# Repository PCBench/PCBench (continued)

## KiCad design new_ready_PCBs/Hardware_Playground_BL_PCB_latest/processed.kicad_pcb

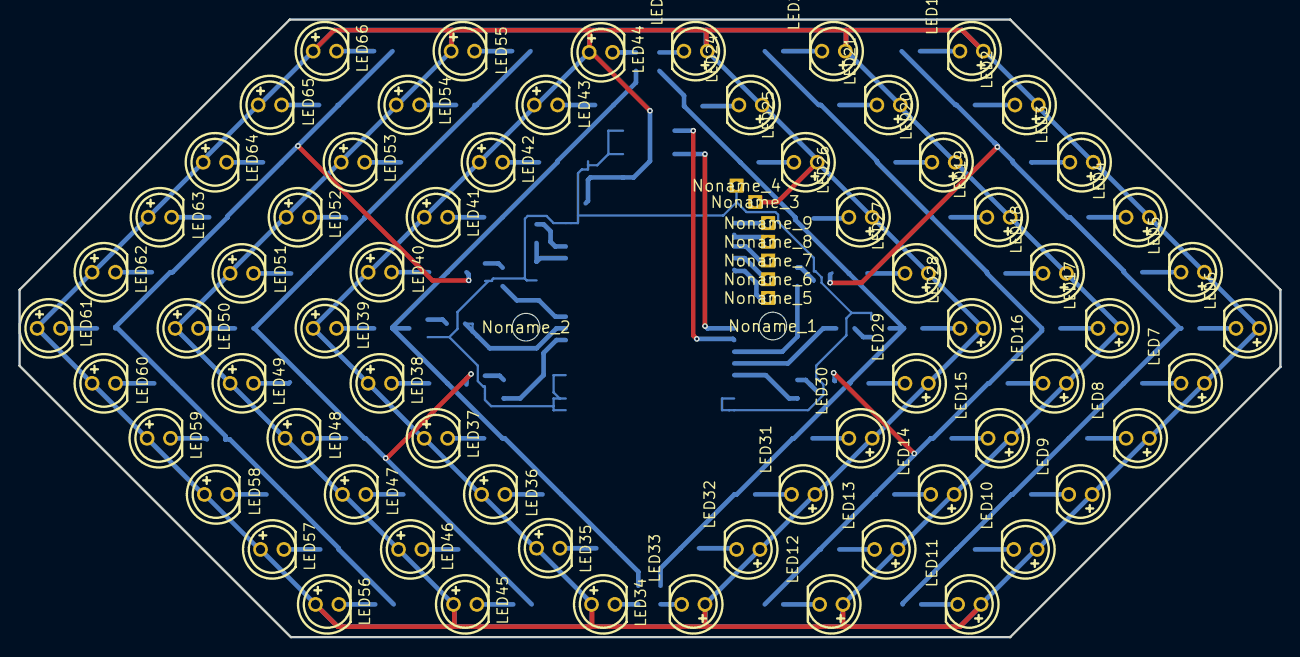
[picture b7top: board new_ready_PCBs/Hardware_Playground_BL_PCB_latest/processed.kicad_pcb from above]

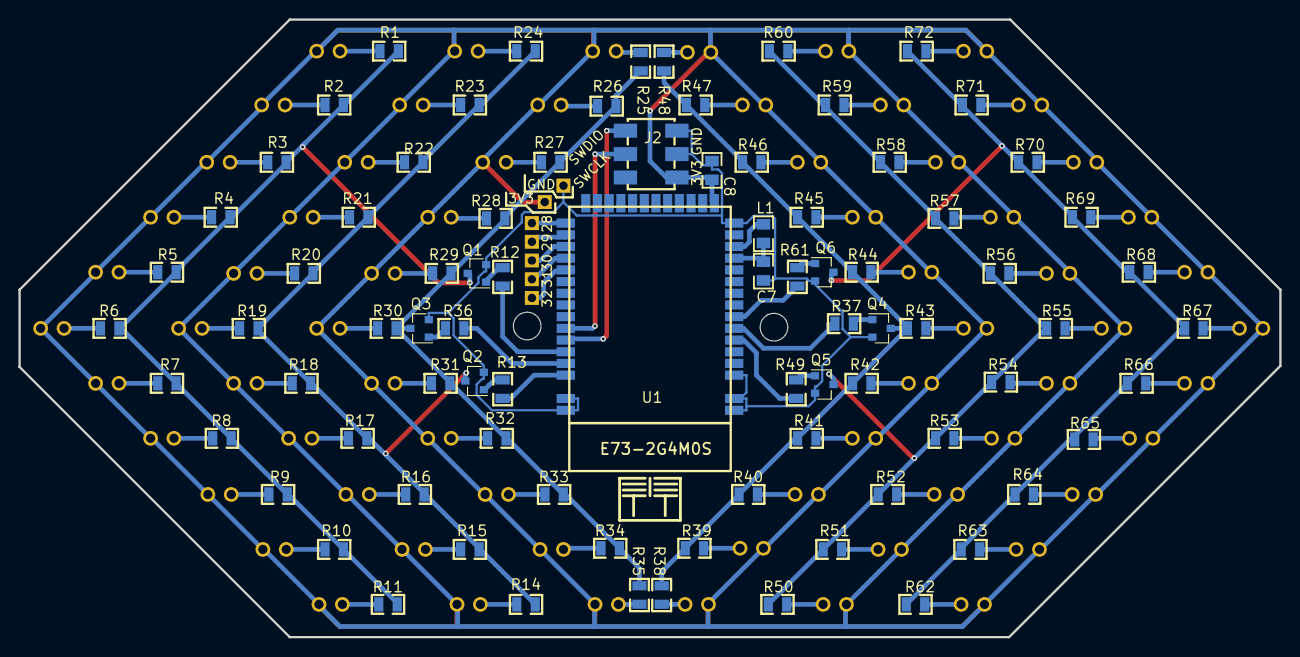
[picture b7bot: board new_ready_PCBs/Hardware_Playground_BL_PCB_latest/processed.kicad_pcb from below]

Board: 2 copper layers, 136.9 x 67.1 mm, 159 parts (6 on the bottom side), 95 nets.

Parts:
C7: 1u; 0805
C8: 10u; 0805
J2: SWD; H2X3-SMD-2.54
L1: 10uH; 0805
LED1, LED2, LED3, LED4, LED5, LED6, LED7, LED8, LED9, LED10, LED11, LED12, LED13, LED14, LED15, LED16, LED17, LED18, LED19, LED20, LED21, LED22, LED23, LED24, LED25, LED26, LED27, LED28, LED29, LED30, LED31, LED32, LED33, LED34, LED35, LED36, LED37, LED38, LED39, LED40, LED41, LED42, LED43, LED44, LED45, LED46, LED47, LED48, LED49, LED50, LED51, LED52, LED53, LED54, LED55, LED56, LED57, LED58, LED59, LED60, LED61, LED62, LED63, LED64, LED65, LED66: HL-503S45FC; LED-TH_BD5.0-P2.54-FD
LG: my_logo; ggeac4e8891367b2b2c
Noname_1, Noname_2: MountingHole_3.00mm
Noname_3, Noname_4, Noname_5, Noname_6, Noname_7, Noname_8, Noname_9: Pad_1.52mm
Q1, Q2, Q3, Q4, Q5, Q6: MMBT2222; SOT-23
R1, R2, R3, R4, R5, R6, R7, R8, R9, R10, R11, R14, R15, R16, R17, R18, R19, R20, R21, R22, R23, R24, R25, R26, R27, R28, R29, R30, R31, R32, R33, R34, R35, R38, R39, R40, R41, R42, R43, R44, R45, R46, R47, R48, R50, R51, R52, R53, R54, R55, R56, R57, R58, R59, R60, R62, R63, R64, R65, R66, R67, R68, R69, R70, R71, R72: 33; R0805
R12, R13, R36, R37, R49, R61: 1K; R0805
U1: E73-2G4M0S; E73-2G4M04S

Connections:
+3V3: C8.2, J2.1, LED1.1, LED2.1, LED3.1, LED4.1, LED5.1, LED6.1, LED7.1, LED8.1, LED9.1, LED10.1, LED11.1, LED12.1, LED13.1, LED14.1, LED15.1, LED16.1, LED17.1, LED18.1, LED19.1, LED20.1, LED21.1, LED22.1, LED23.1, LED24.1, LED25.1, LED26.1, LED27.1, LED28.1, LED29.1, LED30.1, LED31.1, LED32.1, LED33.1, LED34.1, LED35.1, LED36.1, LED37.1, LED38.1, LED39.1, LED40.1, LED41.1, LED42.1, LED43.1, LED44.1, LED45.1, LED46.1, LED47.1, LED48.1, LED49.1, LED50.1, LED51.1, LED52.1, LED53.1, LED54.1, LED55.1, LED56.1, LED57.1, LED58.1, LED59.1, LED60.1, LED61.1, LED62.1, LED63.1, LED64.1, LED65.1, LED66.1, Noname_3.3, U1.16
AL1: R12.1, U1.39
AL2: R13.1, U1.41
AL3: R36.1, U1.40
AR1: R37.1, U1.6
AR2: R49.1, U1.5
AR3: R61.1, U1.7
C7_2: C7.2, L1.1, U1.12
GND: C7.1, C8.1, J2.2, J2.3, Noname_4.2, Q1.2, Q2.2, Q3.2, Q4.2, Q5.2, Q6.2, U1.0, U1.1, U1.2, U1.15, U1.42, U1.43
L1_2: L1.2, U1.13
LED1_2: LED1.2, R1.2
LED2_2: LED2.2, R2.2
LED3_2: LED3.2, R3.2
LED4_2: LED4.2, R4.2
LED5_2: LED5.2, R5.2
LED6_2: LED6.2, R6.2
LED7_2: LED7.2, R7.2
LED8_2: LED8.2, R8.2
LED9_2: LED9.2, R9.2
LED10_2: LED10.2, R10.2
LED11_2: LED11.2, R11.2
LED23_2: LED23.2, R25.2
LED24_2: LED24.2, R26.2
LED25_2: LED25.2, R27.2
LED26_2: LED26.2, R28.2
LED27_2: LED27.2, R29.2
LED28_2: LED28.2, R30.2
LED29_2: LED29.2, R31.2
LED30_2: LED30.2, R32.2
LED31_2: LED31.2, R33.2
LED32_2: LED32.2, R34.2
LED33_2: LED33.2, R35.2
unnamed: Noname_9.1, U1.28
unnamed: Noname_8.1, U1.29
unnamed: Noname_7.1, U1.30
unnamed: Noname_6.1, U1.31
unnamed: Noname_5.1, U1.32
Q1_1: Q1.1, R12.2
Q2_3: Q2.3, R14.1, R15.1, R16.1, R17.1, R18.1, R19.1, R20.1, R21.1, R22.1, R23.1, R24.1
Q3_1: Q3.1, R36.2
Q4_3: Q4.3, R38.1, R39.1, R40.1, R41.1, R42.1, R43.1, R44.1, R45.1, R46.1, R47.1, R48.1
Q5_3: Q5.3, R50.1, R51.1, R52.1, R53.1, R54.1, R55.1, R56.1, R57.1, R58.1, R59.1, R60.1
Q6_3: Q6.3, R62.1, R63.1, R64.1, R65.1, R66.1, R67.1, R68.1, R69.1, R70.1, R71.1, R72.1
R1_1: Q1.3, R1.1, R2.1, R3.1, R4.1, R5.1, R6.1, R7.1, R8.1, R9.1, R10.1, R11.1
R13_2: Q2.1, R13.2
R14_2: LED12.2, R14.2
R15_2: LED13.2, R15.2
R16_2: LED14.2, R16.2
R17_2: LED15.2, R17.2
R18_2: LED16.2, R18.2
R19_2: LED17.2, R19.2
R20_2: LED18.2, R20.2
R21_2: LED19.2, R21.2
R22_2: LED20.2, R22.2
R23_2: LED21.2, R23.2
R24_2: LED22.2, R24.2
R25_1: Q3.3, R25.1, R26.1, R27.1, R28.1, R29.1, R30.1, R31.1, R32.1, R33.1, R34.1, R35.1
R37_2: Q4.1, R37.2
R38_2: LED34.2, R38.2
R39_2: LED35.2, R39.2
R40_2: LED36.2, R40.2
R41_2: LED37.2, R41.2
R42_2: LED38.2, R42.2
R43_2: LED39.2, R43.2
R44_2: LED40.2, R44.2
R45_2: LED41.2, R45.2
R46_2: LED42.2, R46.2
R47_2: LED43.2, R47.2
R48_2: LED44.2, R48.2
R49_2: Q5.1, R49.2
R50_2: LED45.2, R50.2
R51_2: LED46.2, R51.2
R52_2: LED47.2, R52.2
R53_2: LED48.2, R53.2
R54_2: LED49.2, R54.2
R55_2: LED50.2, R55.2
R56_2: LED51.2, R56.2
R57_2: LED52.2, R57.2
R58_2: LED53.2, R58.2
R59_2: LED54.2, R59.2
R60_2: LED55.2, R60.2
R61_2: Q6.1, R61.2
R62_2: LED56.2, R62.2
R63_2: LED57.2, R63.2
R64_2: LED58.2, R64.2
R65_2: LED59.2, R65.2
R66_2: LED60.2, R66.2
R67_2: LED61.2, R67.2
R68_2: LED62.2, R68.2
R69_2: LED63.2, R69.2
R70_2: LED64.2, R70.2
R71_2: LED65.2, R71.2
R72_2: LED66.2, R72.2
SWCLK: J2.5, U1.37
SWDIO: J2.4, U1.38

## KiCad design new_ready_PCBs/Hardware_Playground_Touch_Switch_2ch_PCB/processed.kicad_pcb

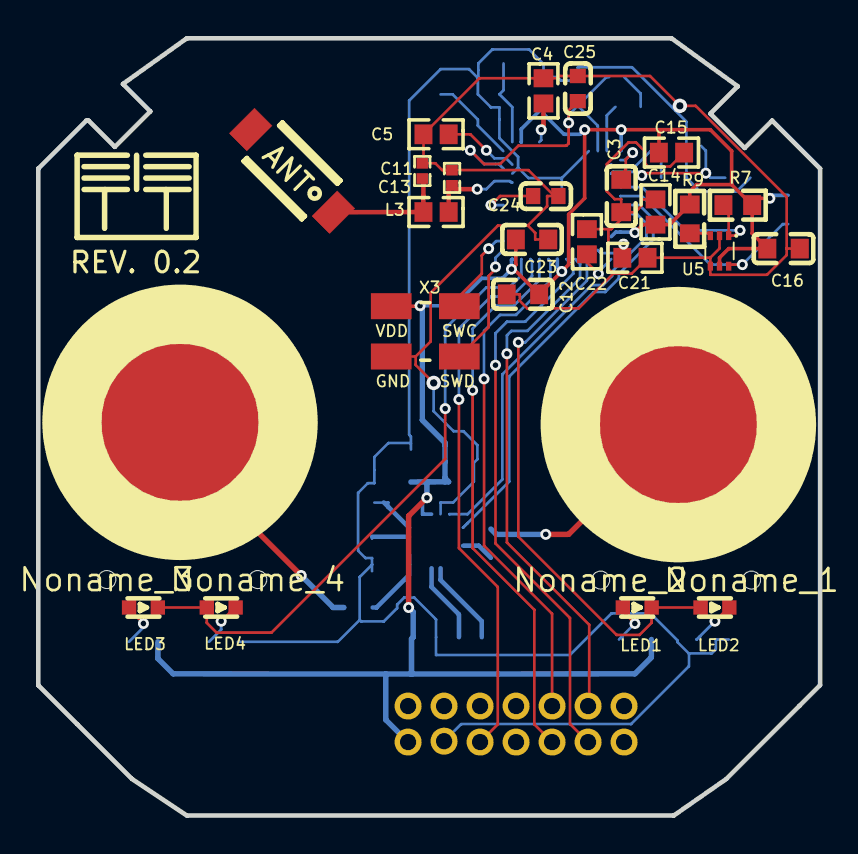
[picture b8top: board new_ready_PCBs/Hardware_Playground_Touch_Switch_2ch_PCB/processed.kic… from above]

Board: 2 copper layers, 43.4 x 43.2 mm, 57 parts (0 on the bottom side), 43 nets.

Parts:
ALG: my_logo; ggeac4e8891367b2b2c
C1, C15, C17: 1uF; 0603
C2, C3, C12, C16, C18, C19, C20, C23: 100nF; C0603
C4: N.C.; 0603
C5: 100pF; 0603
C6: 2.2nF; C0603
C7, C8, C9, C10: 22pF; 0603
C11: 0.8pF; 0402
C13: 0.5pF; 0402
C14, C21, C22: 4.7uF; 0603
C24: 820pF; C0603
C25: 47nF; C0603
CN1: 2X7P; HDR-TH_14P-P2.00-V-R2-C7-S2.00_A2005HWV-2X7P
H1: PROG; CONNECTER_SMD_1.27_1X4_D180
L2: 10uH; 0603
L3: 4.7nH; 0603
L4: 15nH; 0402
LED1, LED3: RED; LED-SMD_0603-T
LED2, LED4: BLUE; LED-SMD_0603-T
Noname_1, Noname_2, Noname_3, Noname_4: MountingHole_1.00mm
R1, R2, R5, R6, R7, R8, R9: 4.7K; R0603
R3, R10: 560; R0603
U1: NRF52840-QIAA-R; AQFN-73_L7.0-W7.0-P0.50-BL-EP4.8
U2, U7: TS1; LIVOLO_TOUCH_PAD
U3: Antenna 2.4GHz; AN6520
U5: TMP112; SOT-563_L1.6-W1.2-P0.50-LS1.6-BL
U6: CY8C4014LQI-421T; QFN-16_L3.0-W3.0-P0.50-BL-EP1.7
X1: 32MHz; OSC-SMD_4P-L2.0-W1.6-BL
X2: 32.768KHz; FC-135R_L3.2-W1.5
X3: ICSP; SWD4_5032

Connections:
ANT: C11.1, L3.1, U1.H23
C4_2: C4.2, U1.A18
CH1_LED: LED1.1, LED2.2, U1.AD8
CH2_LED: LED3.1, LED4.2, U1.AD22
DCC: L2.1, U1.B3
DEC4_6: C1.1, C25.2, L4.2, U1.B5, U1.E24
GND: C1.2, C2.1, C3.2, C4.1, C5.2, C6.2, C7.2, C8.2, C9.1, C10.1, C11.2, C12.1, C13.2, C14.2, C15.1, C16.2, C17.1, C18.1, C19.1, C20.1, C21.1, C22.1, C23.1, C24.1, C25.1, CN1.11, H1.3, R2.2, R5.2, U1.0, U1.B7, U1.F23, U5.2, U5.4, U6.7, X1.2, X1.4, X3.3
L2_2: L2.2, L4.1
L3_2: C13.1, L3.2, U3.1
LED2_1: LED2.1, R5.1
LED3_2: LED3.2, R1.1
MTO1: U1.R1, U6.8
MTO2: U1.N1, U6.9
R1_RST: CN1.6, U1.AD16
R1_SET: CN1.4, U1.AD10
R2_1: LED4.1, R2.1
R2_RST: CN1.3, U1.AD12
R2_SET: CN1.5, U1.AD18
R3_1: R3.1, U2.1
R6_1: LED1.2, R6.1
R9_1: R9.1, U5.3
R10_1: R10.1, U7.1
SCL: R7.2, U1.J1, U5.1
SDA: R8.2, U1.L1, U5.6
SWC: H1.2, U6.15
SWCLK: U1.AA24, X3.1
SWD: H1.1, U6.14
SWDIO: U1.AC24, X3.4
U1_AC5: C21.2, U1.AC5
U1_AD2: C22.2, U1.AD2
U1_C1: C3.1, U1.C1
U1_D23: C5.1, U1.D23
U1_N24: C24.2, U1.N24
U6_1: R3.2, U6.1
U6_3: C6.1, U6.3
U6_4: C19.2, U6.4
U6_11: R10.2, U6.11
VDD: C2.2, C12.2, C14.1, C15.2, C16.1, C17.2, C18.2, C20.2, C23.2, CN1.13, H1.4, R1.2, R6.2, R7.1, R8.1, R9.2, U1.A22, U1.AD14, U1.AD23, U1.B1, U1.W1, U1.Y2, U5.5, U6.5, U6.6, X3.2
VSENSE: CN1.9, U1.AD20
XC1: C7.1, U1.B24, X1.1
XC2: C8.1, U1.A23, X1.3
XL1: C9.2, U1.D2, X2.1
XL2: C10.2, U1.F2, X2.2
